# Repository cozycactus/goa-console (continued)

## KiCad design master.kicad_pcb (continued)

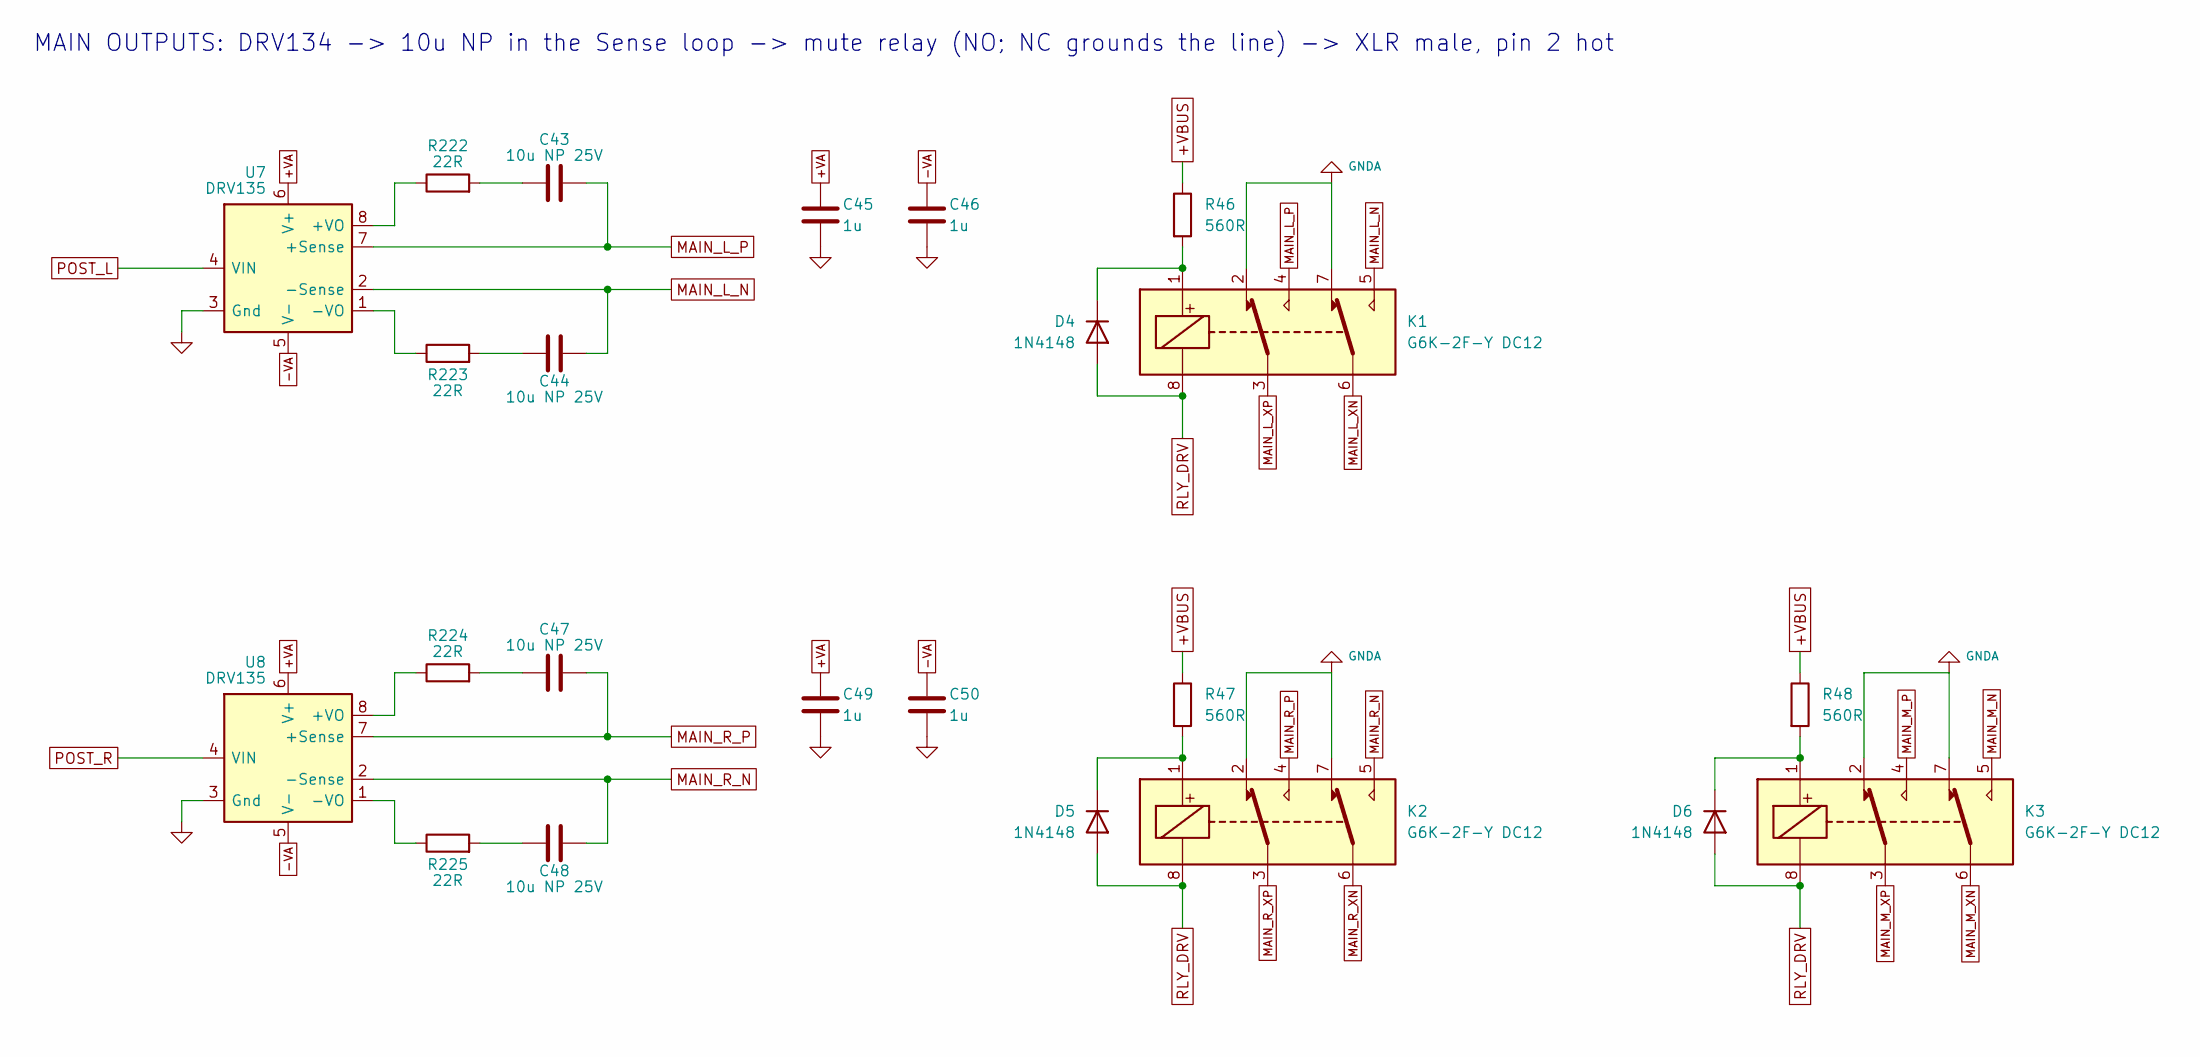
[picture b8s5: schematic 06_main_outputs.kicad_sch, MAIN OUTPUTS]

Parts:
C43, C44, C47, C48: 10u NP 25V; CP_Radial_D5.0mm_P2.00mm; MPN Panasonic ECE-A1EN100U (matched pair: t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
C45, C46, C49, C50: 1u; C_1206_3216Metric; MPN Samsung CL31B105KBHNNNE (X7R 50V)
D4, D5, D6: 1N4148; D_DO-35_SOD27_P7.62mm_Horizontal; MPN Vishay 1N4148-TAP
K1, K2, K3: G6K-2F-Y DC12; Relay_DPDT_Omron_G6K-2F-Y; MPN Omron G6K-2F-Y DC12
R46, R47, R48: 560R; R_0805_2012Metric
R222, R223, R224, R225: 22R; R_0805_2012Metric; MPN Panasonic ERJ-P06J220V
U7, U8: DRV135; SOIC-8_3.9x4.9mm_P1.27mm; MPN TI DRV135UA

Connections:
+VA: C45.1, C49.1, U7.6 (V+), U8.6 (V+); also elsewhere on the board
+VBUS: R46.1, R47.1, R48.1; also elsewhere on the board
-VA: C46.2, C50.2, U7.5 (V-), U8.5 (V-); also elsewhere on the board
MAIN_L_N: C44.2, K1.5, U7.2 (-Sense)
MAIN_L_P: C43.2, K1.4, U7.7 (+Sense)
MAIN_L_XN: K1.6; also elsewhere on the board
MAIN_L_XP: K1.3; also elsewhere on the board
MAIN_M_N: K3.5; also elsewhere on the board
MAIN_M_P: K3.4; also elsewhere on the board
MAIN_M_XN: K3.6; also elsewhere on the board
MAIN_M_XP: K3.3; also elsewhere on the board
MAIN_R_N: C48.2, K2.5, U8.2 (-Sense)
MAIN_R_P: C47.2, K2.4, U8.7 (+Sense)
MAIN_R_XN: K2.6; also elsewhere on the board
MAIN_R_XP: K2.3; also elsewhere on the board
unnamed: C43.1, R222.2
unnamed: C44.1, R223.2
unnamed: C47.1, R224.2
unnamed: C48.1, R225.2
unnamed: D4.1 (K), K1.1, R46.2
unnamed: D5.1 (K), K2.1, R47.2
unnamed: D6.1 (K), K3.1, R48.2
unnamed: R222.1, U7.8 (+VO)
unnamed: R223.1, U7.1 (-VO)
unnamed: R224.1, U8.8 (+VO)
unnamed: R225.1, U8.1 (-VO)
POST_L: U7.4 (VIN); also elsewhere on the board
POST_R: U8.4 (VIN); also elsewhere on the board
RLY_DRV: D4.2 (A), D5.2 (A), D6.2 (A), K1.8, K2.8, K3.8; also elsewhere on the board

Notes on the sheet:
MAIN OUTPUTS: DRV134 -> 10u NP in the Sense loop -> mute relay (NO; NC grounds the line) -> XLR male, pin 2 hot

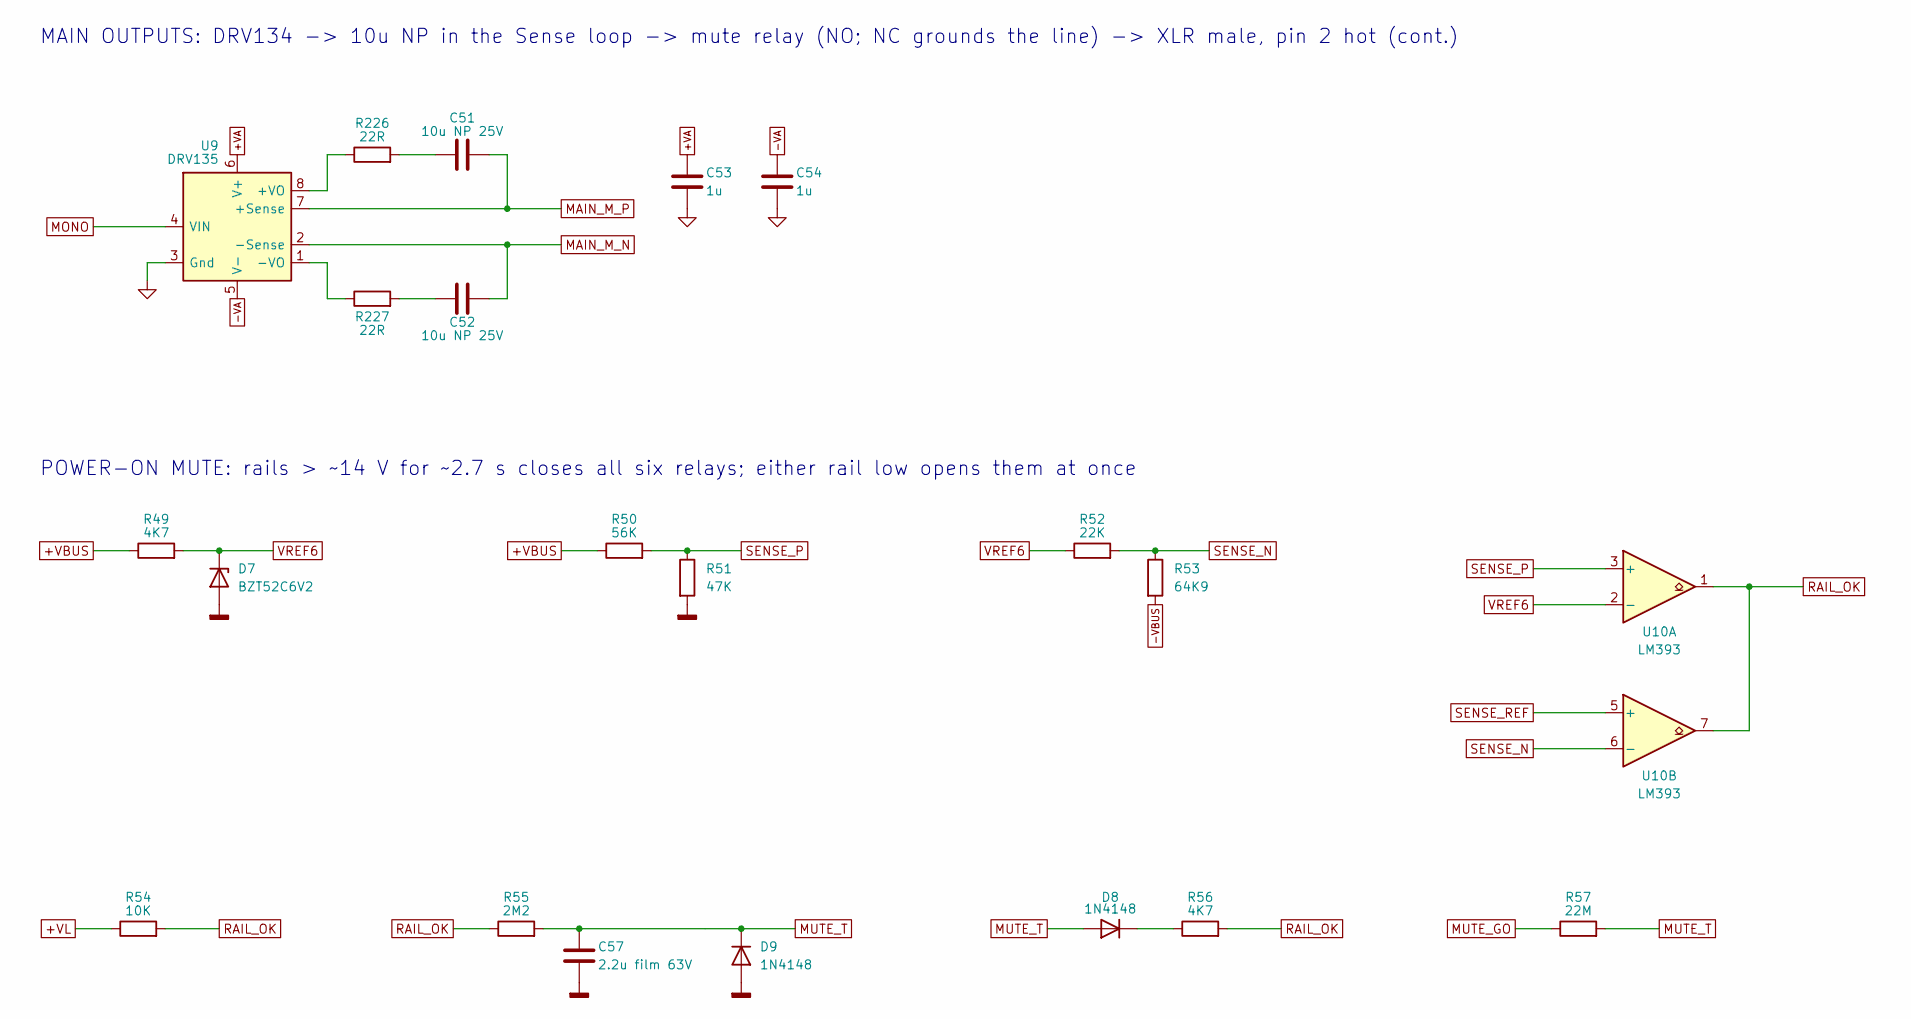
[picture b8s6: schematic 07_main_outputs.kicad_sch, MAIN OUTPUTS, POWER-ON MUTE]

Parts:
C51, C52: 10u NP 25V; CP_Radial_D5.0mm_P2.00mm; MPN Panasonic ECE-A1EN100U (matched pair: t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
C53, C54: 1u; C_1206_3216Metric; MPN Samsung CL31B105KBHNNNE (X7R 50V)
C57: 2.2u film 63V; C_Rect_L7.2mm_W7.2mm_P5.00mm_FKS2_FKP2_MKS2_MKP2; MPN KEMET MMK5225K63J06L4BULK (PET 63V; rep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
D7: BZT52C6V2; D_SOD-123; MPN Diodes BZT52C6V2-7-F
D8, D9: 1N4148; D_DO-35_SOD27_P7.62mm_Horizontal; MPN Vishay 1N4148-TAP
R49, R56: 4K7; R_0805_2012Metric
R50: 56K; R_0805_2012Metric
R51: 47K; R_0805_2012Metric
R52: 22K; R_0805_2012Metric
R53: 64K9; R_0805_2012Metric
R54: 10K; R_0805_2012Metric; MPN Panasonic ERJ-P06J103V
R55: 2M2; R_0805_2012Metric
R57: 22M; R_0805_2012Metric; MPN Yageo RC0805JR-0722ML
R226, R227: 22R; R_0805_2012Metric; MPN Panasonic ERJ-P06J220V
U9: DRV135; SOIC-8_3.9x4.9mm_P1.27mm; MPN TI DRV135UA
U10: LM393; SOIC-8_3.9x4.9mm_P1.27mm; MPN TI LM393BIDR

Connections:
+VA: C53.1, U9.6 (V+); also elsewhere on the board
+VBUS: R49.1, R50.1; also elsewhere on the board
+VL: R54.1; also elsewhere on the board
-VA: C54.2, U9.5 (V-); also elsewhere on the board
-VBUS: R53.2; also elsewhere on the board
GNDD: C57.2, D7.2 (A), D9.2 (A), R51.2; also elsewhere on the board
MAIN_M_N: C52.2, U9.2 (-Sense); also elsewhere on the board
MAIN_M_P: C51.2, U9.7 (+Sense); also elsewhere on the board
MONO: U9.4 (VIN); also elsewhere on the board
MUTE_GO: R57.1; also elsewhere on the board
MUTE_T: C57.1, D8.2 (A), D9.1 (K), R55.2, R57.2; also elsewhere on the board
unnamed: C51.1, R226.2
unnamed: C52.1, R227.2
unnamed: D8.1 (K), R56.1
unnamed: R226.1, U9.8 (+VO)
unnamed: R227.1, U9.1 (-VO)
RAIL_OK: R54.2, R55.1, R56.2, U10.1, U10.7; also elsewhere on the board
SENSE_N: R52.2, R53.1, U10.6 (-)
SENSE_P: R50.2, R51.1, U10.3 (+)
SENSE_REF: U10.5 (+); also elsewhere on the board
VREF6: D7.1 (K), R49.2, R52.1, U10.2 (-); also elsewhere on the board

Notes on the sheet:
MAIN OUTPUTS: DRV134 -> 10u NP in the Sense loop -> mute relay (NO; NC grounds the line) -> XLR male, pin 2 hot (cont.)
POWER-ON MUTE: rails > ~14 V for ~2.7 s closes all six relays; either rail low opens them at once

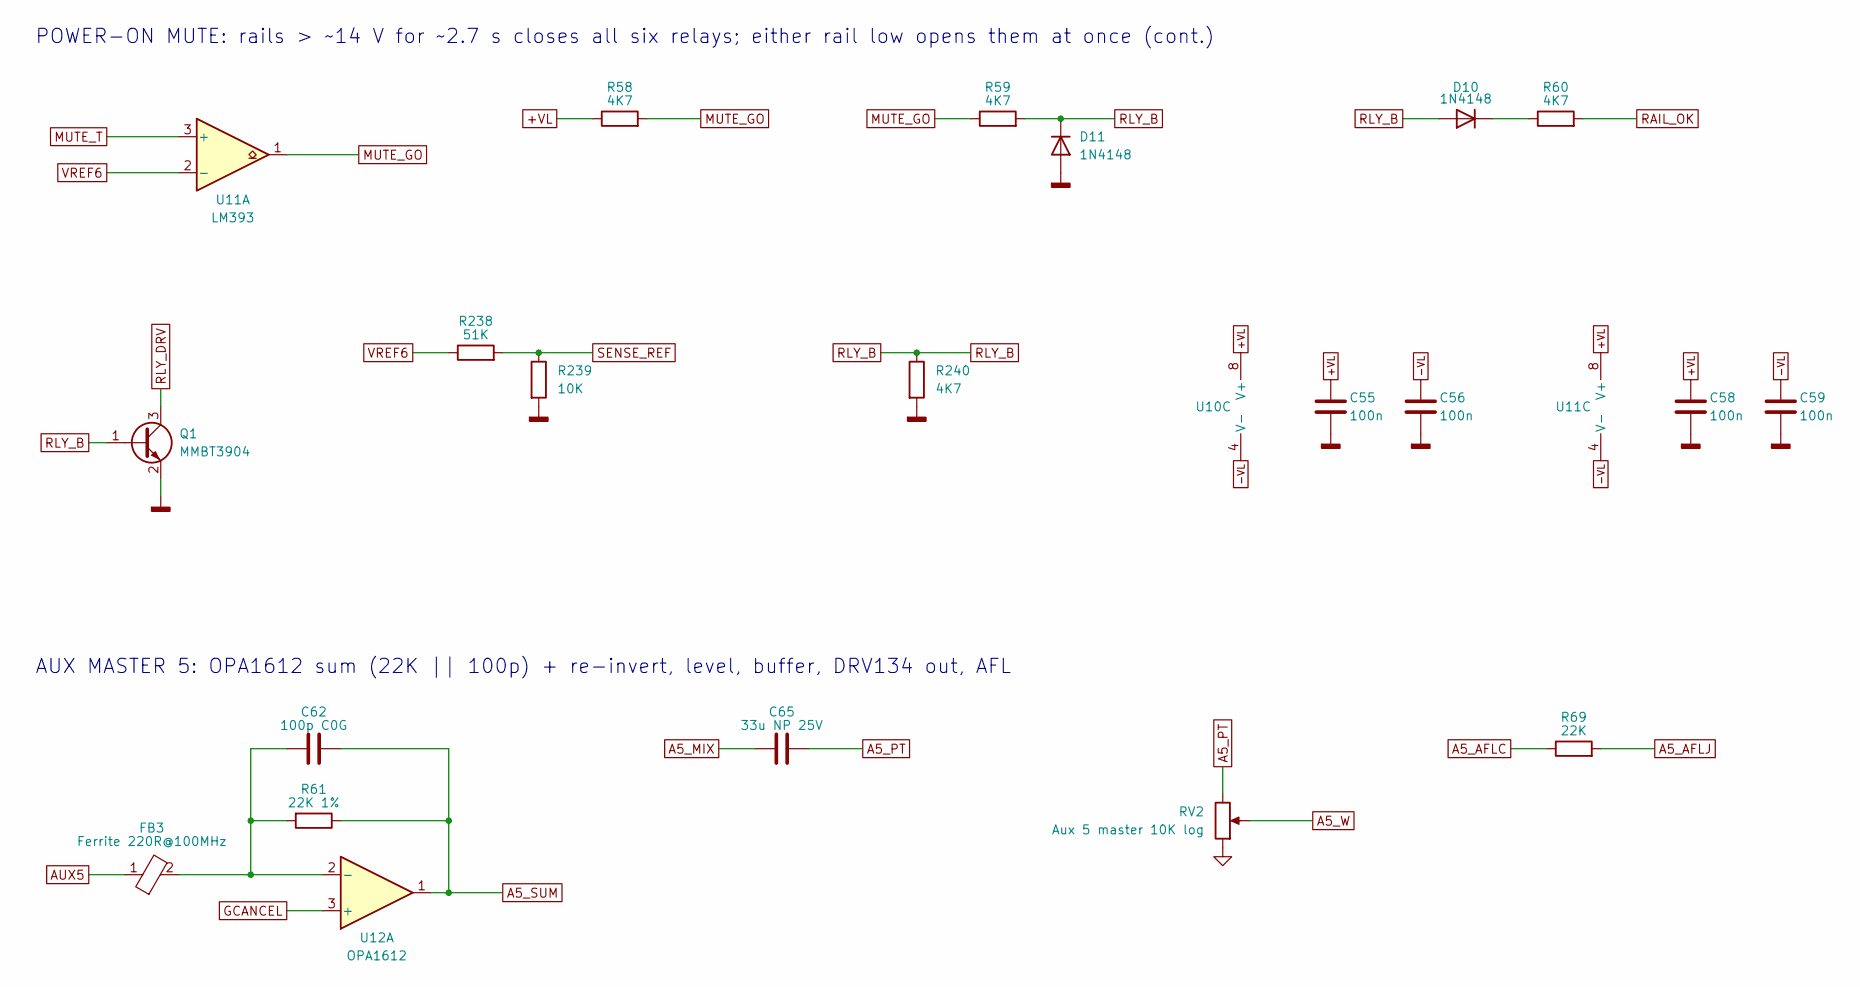
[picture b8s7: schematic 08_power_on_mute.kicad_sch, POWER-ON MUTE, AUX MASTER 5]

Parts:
C55, C56, C58, C59: 100n; C_0805_2012Metric; MPN Samsung CL21B104KBCNNNC (X7R 50V)
C62: 100p C0G; C_0805_2012Metric; MPN KEMET C0805C101J5GACTU
C65: 33u NP 25V; CP_Radial_D8.0mm_P3.50mm; MPN Nichicon UES1E330MPM (MUSE ES)
D10, D11: 1N4148; D_DO-35_SOD27_P7.62mm_Horizontal; MPN Vishay 1N4148-TAP
FB3: Ferrite 220R@100MHz; L_0805_2012Metric; MPN Murata BLM21PG221SN1D
Q1: MMBT3904; SOT-23; MPN onsemi MMBT3904LT1G
R58: 4K7; R_0805_2012Metric; MPN Panasonic ERJ-P06J472V
R59, R60, R240: 4K7; R_0805_2012Metric
R61: 22K 1%; R_0805_2012Metric
R69: 22K; R_0805_2012Metric
R238: 51K; R_0805_2012Metric
R239: 10K; R_0805_2012Metric
RV2: Aux 5 master 10K log; Potentiometer_Alpha_RD901F-40-00D_Single_Vertical; MPN Alpha RD901F-40-15R1-A10K
U10, U11: LM393; SOIC-8_3.9x4.9mm_P1.27mm; MPN TI LM393BIDR
U12: OPA1612; SOIC-8_3.9x4.9mm_P1.27mm; MPN TI OPA1612AIDR

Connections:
+VL: C55.1, C58.1, R58.1, U10.8 (V+), U11.8 (V+); also elsewhere on the board
-VL: C56.2, C59.2, U10.4 (V-), U11.4 (V-); also elsewhere on the board
A5_AFLC: R69.1; also elsewhere on the board
A5_AFLJ: R69.2; also elsewhere on the board
A5_MIX: C65.1; also elsewhere on the board
A5_PT: C65.2, RV2.3
A5_SUM: C62.1, R61.1, U12.1; also elsewhere on the board
A5_W: RV2.2; also elsewhere on the board
AUX5: FB3.1; also elsewhere on the board
GCANCEL: U12.3 (+); also elsewhere on the board
GNDD: C55.2, C56.1, C58.2, C59.1, D11.2 (A), Q1.2 (E), R239.2, R240.2; also elsewhere on the board
MUTE_GO: R58.2, R59.1, U11.1; also elsewhere on the board
MUTE_T: U11.3 (+); also elsewhere on the board
unnamed: D10.1 (K), R60.1
unnamed: C62.2, FB3.2, R61.2, U12.2 (-)
RAIL_OK: R60.2; also elsewhere on the board
RLY_B: D10.2 (A), D11.1 (K), Q1.1 (B), R59.2, R240.1
RLY_DRV: Q1.3 (C); also elsewhere on the board
SENSE_REF: R238.2, R239.1; also elsewhere on the board
VREF6: R238.1, U11.2 (-); also elsewhere on the board

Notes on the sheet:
POWER-ON MUTE: rails > ~14 V for ~2.7 s closes all six relays; either rail low opens them at once (cont.)
AUX MASTER 5: OPA1612 sum (22K || 100p) + re-invert, level, buffer, DRV134 out, AFL

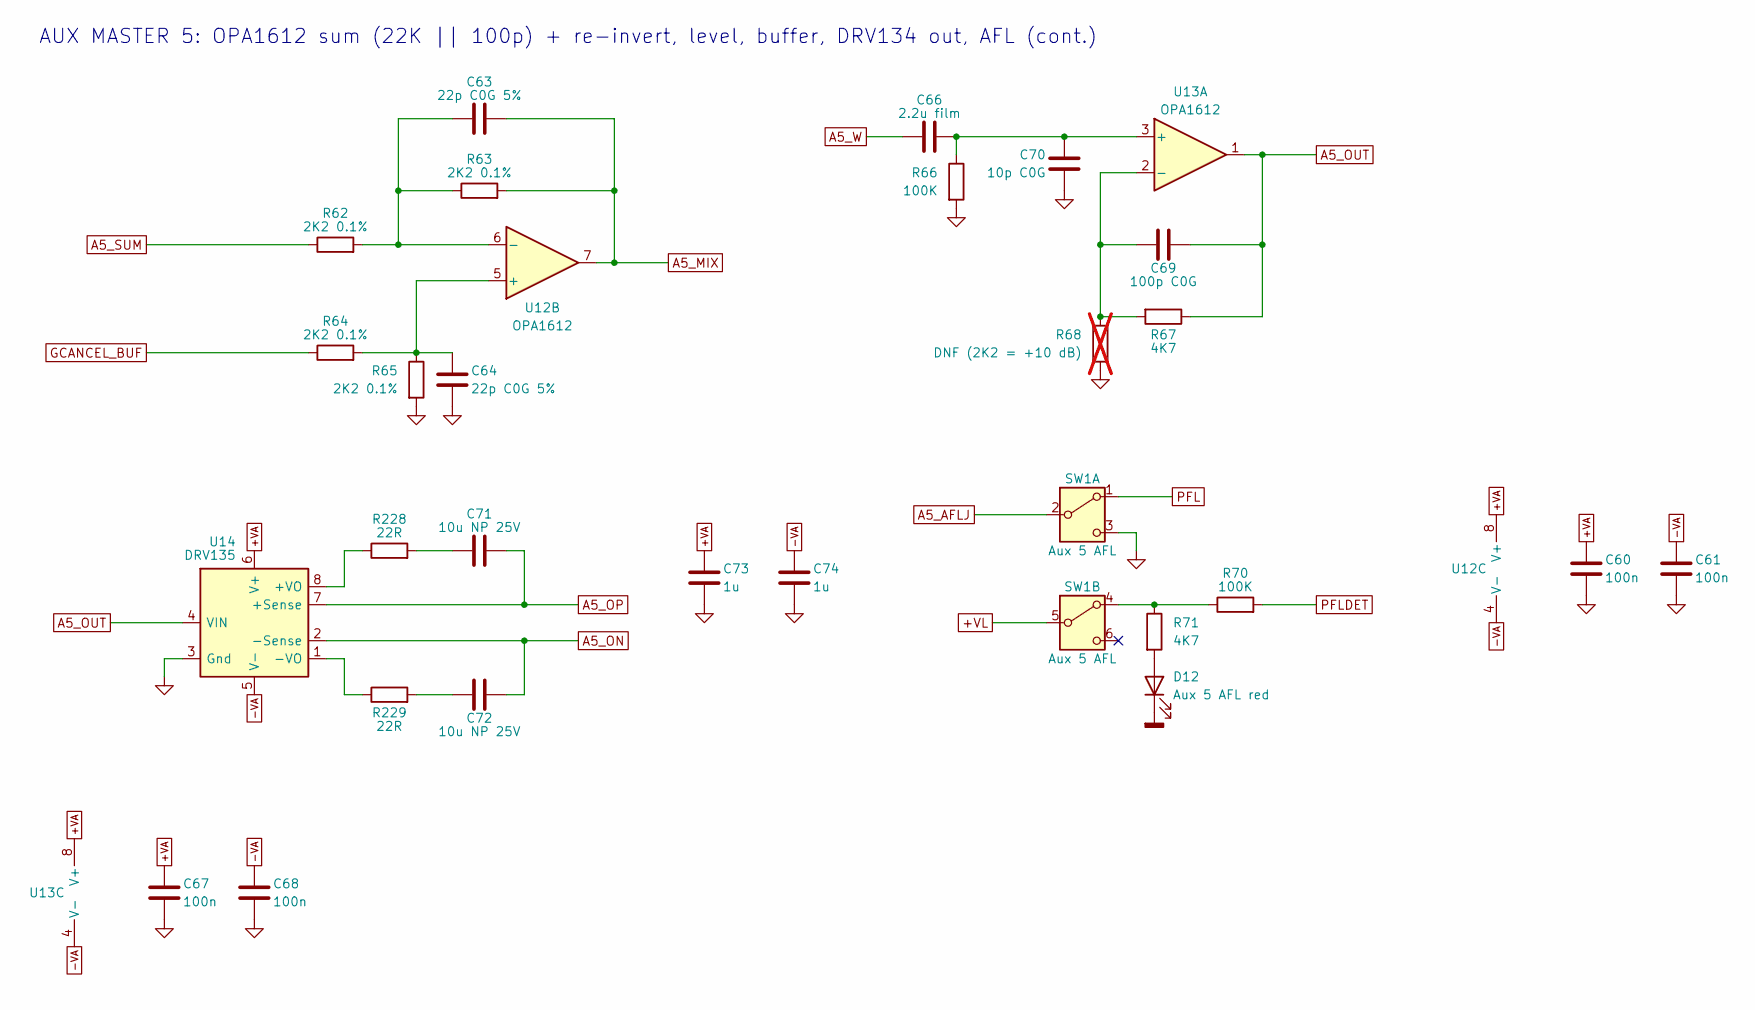
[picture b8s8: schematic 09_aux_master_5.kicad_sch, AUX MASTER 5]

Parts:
C60, C61, C67, C68: 100n; C_0805_2012Metric; MPN Samsung CL21B104KBCNNNC (X7R 50V)
C63, C64: 22p C0G 5%; C_0805_2012Metric; MPN KEMET C0805C220J5GACTU
C66: 2.2u film; C_Rect_L7.2mm_W7.2mm_P5.00mm_FKS2_FKP2_MKS2_MKP2; MPN KEMET MMK5225K63J06L4BULK (PET 63V; rep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
C69: 100p C0G; C_0805_2012Metric; MPN KEMET C0805C101J5GACTU
C70: 10p C0G; C_0805_2012Metric; MPN KEMET C0805C100J5GACTU
C71, C72: 10u NP 25V; CP_Radial_D5.0mm_P2.00mm; MPN Panasonic ECE-A1EN100U (matched pair: t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
C73, C74: 1u; C_1206_3216Metric; MPN Samsung CL31B105KBHNNNE (X7R 50V)
D12: Aux 5 AFL red; LED_D3.0mm; MPN Kingbright WP710A10ID
R62, R63, R64, R65: 2K2 0.1%; R_0805_2012Metric; MPN Panasonic ERA-6AEB222V
R66, R70: 100K; R_0805_2012Metric
R67, R71: 4K7; R_0805_2012Metric
R68: DNF (2K2 = +10 dB); R_0805_2012Metric; not fitted
R228, R229: 22R; R_0805_2012Metric; MPN Panasonic ERJ-P06J220V
SW1: Aux 5 AFL; SW_Push_2P2T_Toggle_CK_PVA2xxH1xxxxxxV2; MPN C&K PVA2 EE H1 1.7N V2
U12, U13: OPA1612; SOIC-8_3.9x4.9mm_P1.27mm; MPN TI OPA1612AIDR
U14: DRV135; SOIC-8_3.9x4.9mm_P1.27mm; MPN TI DRV135UA

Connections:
+VA: C60.1, C67.1, C73.1, U12.8 (V+), U13.8 (V+), U14.6 (V+); also elsewhere on the board
+VL: SW1.5 (B); also elsewhere on the board
-VA: C61.2, C68.2, C74.2, U12.4 (V-), U13.4 (V-), U14.5 (V-); also elsewhere on the board
A5_AFLJ: SW1.2 (B); also elsewhere on the board
A5_MIX: C63.1, R63.2, U12.7; also elsewhere on the board
A5_ON: C72.2, U14.2 (-Sense); also elsewhere on the board
A5_OP: C71.2, U14.7 (+Sense); also elsewhere on the board
A5_OUT: C69.1, R67.1, U13.1, U14.4 (VIN); also elsewhere on the board
A5_SUM: R62.1; also elsewhere on the board
A5_W: C66.1; also elsewhere on the board
GCANCEL_BUF: R64.1; also elsewhere on the board
GNDD: D12.1 (K); also elsewhere on the board
unnamed: C71.1, R228.2
unnamed: C72.1, R229.2
unnamed: D12.2 (A), R71.2
unnamed: R70.1, R71.1, SW1.4 (A)
unnamed: C64.1, R64.2, R65.1, U12.5 (+)
unnamed: C63.2, R62.2, R63.1, U12.6 (-)
unnamed: C66.2, C70.1, R66.1, U13.3 (+)
unnamed: C69.2, R67.2, R68.1, U13.2 (-)
unnamed: R228.1, U14.8 (+VO)
unnamed: R229.1, U14.1 (-VO)
PFL: SW1.1 (A); also elsewhere on the board
PFLDET: R70.2; also elsewhere on the board

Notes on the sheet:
AUX MASTER 5: OPA1612 sum (22K || 100p) + re-invert, level, buffer, DRV134 out, AFL (cont.)

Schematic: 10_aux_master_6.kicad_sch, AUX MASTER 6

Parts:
C75, C76: 100n; C_0805_2012Metric; MPN Samsung CL21B104KBCNNNC (X7R 50V)
C77, C82: 100p C0G; C_0805_2012Metric; MPN KEMET C0805C101J5GACTU
C78, C79: 22p C0G 5%; C_0805_2012Metric; MPN KEMET C0805C220J5GACTU
C80: 33u NP 25V; CP_Radial_D8.0mm_P3.50mm; MPN Nichicon UES1E330MPM (MUSE ES)
C81: 2.2u film; C_Rect_L7.2mm_W7.2mm_P5.00mm_FKS2_FKP2_MKS2_MKP2; MPN KEMET MMK5225K63J06L4BULK (PET 63V; rep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
C83: 10p C0G; C_0805_2012Metric; MPN KEMET C0805C100J5GACTU
C84, C85: 10u NP 25V; CP_Radial_D5.0mm_P2.00mm; MPN Panasonic ECE-A1EN100U (matched pair: t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
C86, C87: 1u; C_1206_3216Metric; MPN Samsung CL31B105KBHNNNE (X7R 50V)
FB4: Ferrite 220R@100MHz; L_0805_2012Metric; MPN Murata BLM21PG221SN1D
R72: 22K 1%; R_0805_2012Metric
R73, R74, R75, R76: 2K2 0.1%; R_0805_2012Metric; MPN Panasonic ERA-6AEB222V
R77: 100K; R_0805_2012Metric
R78: 4K7; R_0805_2012Metric
R79: DNF (2K2 = +10 dB); R_0805_2012Metric; not fitted
R80: 22K; R_0805_2012Metric
R230, R231: 22R; R_0805_2012Metric; MPN Panasonic ERJ-P06J220V
RV3: Aux 6 master 10K log; Potentiometer_Alpha_RD901F-40-00D_Single_Vertical; MPN Alpha RD901F-40-15R1-A10K
U13, U15: OPA1612; SOIC-8_3.9x4.9mm_P1.27mm; MPN TI OPA1612AIDR
U16: DRV135; SOIC-8_3.9x4.9mm_P1.27mm; MPN TI DRV135UA

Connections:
+VA: C75.1, C86.1, U15.8 (V+), U16.6 (V+); also elsewhere on the board
-VA: C76.2, C87.2, U15.4 (V-), U16.5 (V-); also elsewhere on the board
A6_AFLJ: R80.2; also elsewhere on the board
A6_MIX: C78.1, C80.1, R74.2, U15.7
A6_ON: C85.2, U16.2 (-Sense); also elsewhere on the board
A6_OP: C84.2, U16.7 (+Sense); also elsewhere on the board
A6_PT: C80.2, RV3.3
A6_SUM: C77.1, R72.1, R73.1, U15.1
A6_W: C81.1, RV3.2
AUX6: FB4.1; also elsewhere on the board
GCANCEL: U15.3 (+); also elsewhere on the board
GCANCEL_BUF: R75.1; also elsewhere on the board
unnamed: C84.1, R230.2
unnamed: C85.1, R231.2
unnamed: C81.2, C83.1, R77.1, U13.5 (+)
unnamed: C82.2, R78.2, R79.1, U13.6 (-)
unnamed: C77.2, FB4.2, R72.2, U15.2 (-)
unnamed: C79.1, R75.2, R76.1, U15.5 (+)
unnamed: C78.2, R73.2, R74.1, U15.6 (-)
unnamed: R230.1, U16.8 (+VO)
unnamed: R231.1, U16.1 (-VO)

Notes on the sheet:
AUX MASTER 6: OPA1612 sum (22K || 100p) + re-invert, level, buffer, DRV134 out, AFL

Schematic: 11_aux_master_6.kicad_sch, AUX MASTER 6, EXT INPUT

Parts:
C88, C89: 100p C0G; C_0805_2012Metric; MPN KEMET C0805C101J5GACTU
C90, C91: 33p C0G; C_0805_2012Metric; MPN KEMET C0805C330J5GACTU
C98, C99: 33u NP 25V; CP_Radial_D8.0mm_P3.50mm; MPN Nichicon UES1E330MPM (MUSE ES)
D13: Aux 6 AFL red; LED_D3.0mm; MPN Kingbright WP710A10ID
R81: 100K; R_0805_2012Metric
R82: 4K7; R_0805_2012Metric
R83, R212: 1M; R_0805_2012Metric
R84, R85, R86, R87: 10K 0.1%; R_0805_2012Metric; MPN Panasonic ERA-6AEB103V
R93, R95, R215, R216: 100R; R_0805_2012Metric
R94, R96: 47K; R_0805_2012Metric
R213, R214: 220R; R_0805_2012Metric
SW2: Aux 6 AFL; SW_Push_2P2T_Toggle_CK_PVA2xxH1xxxxxxV2; MPN C&K PVA2 EE H1 1.7N V2
U17: OPA1612; SOIC-8_3.9x4.9mm_P1.27mm; MPN TI OPA1612AIDR
U43: OPA1656; SOIC-8_3.9x4.9mm_P1.27mm; MPN TI OPA1656IDR

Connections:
+VL: SW2.5 (B); also elsewhere on the board
A6_AFLJ: SW2.2 (B); also elsewhere on the board
EXT_BL: C90.2, R85.2, R93.1, U17.1
EXT_BL_RB: R84.1, R216.2
EXT_BL_TB: R86.1, R215.2
EXT_BR: R95.1; also elsewhere on the board
EXT_L: C98.2, R94.1; also elsewhere on the board
EXT_LR: R212.1, R214.1; also elsewhere on the board
EXT_LT: R83.1, R213.1; also elsewhere on the board
EXT_R: C99.2, R96.1; also elsewhere on the board
GNDD: D13.1 (K); also elsewhere on the board
unnamed: C98.1, R93.2
unnamed: C99.1, R95.2
unnamed: D13.2 (A), R82.2
unnamed: R81.1, R82.1, SW2.4 (A)
unnamed: C91.1, R86.2, R87.1, U17.3 (+)
unnamed: C90.1, R84.2, R85.1, U17.2 (-)
unnamed: C88.1, R213.2, U43.3 (+)
unnamed: R215.1, U43.1, U43.2 (-)
unnamed: C89.1, R214.2, U43.5 (+)
unnamed: R216.1, U43.6 (-), U43.7
PFL: SW2.1 (A); also elsewhere on the board
PFLDET: R81.2; also elsewhere on the board

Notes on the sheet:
AUX MASTER 6: OPA1612 sum (22K || 100p) + re-invert, level, buffer, DRV134 out, AFL (cont.)
EXT INPUT (2-track / DAW) and MIX / EXT monitor select (SW latched = EXT)

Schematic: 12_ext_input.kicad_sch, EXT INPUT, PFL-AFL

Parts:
C92, C93, C100, C101, C190, C191, C192, C193: 100n; C_0805_2012Metric; MPN Samsung CL21B104KBCNNNC (X7R 50V)
C94, C95: 100p C0G; C_0805_2012Metric; MPN KEMET C0805C101J5GACTU
C96, C97: 33p C0G; C_0805_2012Metric; MPN KEMET C0805C330J5GACTU
C105: 33u NP 25V; CP_Radial_D8.0mm_P3.50mm; MPN Nichicon UES1E330MPM (MUSE ES)
C106: 2.2u film; C_Rect_L7.2mm_W7.2mm_P5.00mm_FKS2_FKP2_MKS2_MKP2; MPN KEMET MMK5225K63J06L4BULK (PET 63V; rep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
C109: 22p C0G; C_0805_2012Metric; MPN KEMET C0805C220J5GACTU
R88, R217: 1M; R_0805_2012Metric
R89, R90, R91, R92: 10K 0.1%; R_0805_2012Metric; MPN Panasonic ERA-6AEB103V
R102: 100K; R_0805_2012Metric
R103, R220, R221: 100R; R_0805_2012Metric
R218, R219: 220R; R_0805_2012Metric
RV4: Solo level 10K log; Potentiometer_Alpha_RD901F-40-00D_Single_Vertical; MPN Alpha RD901F-40-15R1-A10K
SW3: EXT select; SW_Push_2P2T_Toggle_CK_PVA2xxH1xxxxxxV2; MPN C&K PVA2 EE H1 1.7N V2
U17, U19: OPA1612; SOIC-8_3.9x4.9mm_P1.27mm; MPN TI OPA1612AIDR
U18, U43, U44: OPA1656; SOIC-8_3.9x4.9mm_P1.27mm; MPN TI OPA1656IDR

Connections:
+VA: C92.1, C100.1, C190.1, C192.1, U17.8 (V+), U18.8 (V+), U43.8 (V+), U44.8 (V+); also elsewhere on the board
-VA: C93.2, C101.2, C191.2, C193.2, U17.4 (V-), U18.4 (V-), U43.4 (V-), U44.4 (V-); also elsewhere on the board
EXT_BR: C96.2, R90.2, U17.7; also elsewhere on the board
EXT_BR_RB: R89.1, R221.2
EXT_BR_TB: R91.1, R220.2
EXT_L: SW3.1 (A); also elsewhere on the board
EXT_R: SW3.4 (A); also elsewhere on the board
EXT_RR: R217.1, R219.1; also elsewhere on the board
EXT_RT: R88.1, R218.1; also elsewhere on the board
MON_L: SW3.2 (B); also elsewhere on the board
MON_R: SW3.5 (B); also elsewhere on the board
unnamed: C97.1, R91.2, R92.1, U17.5 (+)
unnamed: C96.1, R89.2, R90.1, U17.6 (-)
unnamed: C106.2, C109.1, R102.1, U19.3 (+)
unnamed: R103.1, U19.1, U19.2 (-)
unnamed: C94.1, R218.2, U44.3 (+)
unnamed: R220.1, U44.1, U44.2 (-)
unnamed: C95.1, R219.2, U44.5 (+)
unnamed: R221.1, U44.6 (-), U44.7
PFL_MIX: C105.1; also elsewhere on the board
PFL_PT: C105.2, RV4.3
PFL_SIG: R103.2; also elsewhere on the board
PFL_W: C106.1, RV4.2
POST_L: SW3.3 (C); also elsewhere on the board
POST_R: SW3.6 (C); also elsewhere on the board

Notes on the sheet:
EXT INPUT (2-track / DAW) and MIX / EXT monitor select (cont.)
PFL / AFL: OPA1656 sum (22K || 100p) + re-invert, SOLO LEVEL, follower

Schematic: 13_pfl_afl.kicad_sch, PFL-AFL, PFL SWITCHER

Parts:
C102: 100p C0G; C_0805_2012Metric; MPN KEMET C0805C101J5GACTU
C103, C104: 22p C0G 5%; C_0805_2012Metric; MPN KEMET C0805C220J5GACTU
C107, C108: 100n; C_0805_2012Metric; MPN Samsung CL21B104KBCNNNC (X7R 50V)
C110: 1u; C_1206_3216Metric; MPN Samsung CL31B105KBHNNNE (X7R 50V)
C111, C112, C113, C114: 33u NP 25V; CP_Radial_D8.0mm_P3.50mm; MPN Nichicon UES1E330MPM (MUSE ES)
D14: BZX84C5V1; SOT-23; MPN Diodes BZX84C5V1-7-F
D15: BAT54W; SOT-323_SC-70; MPN Nexperia BAT54W,115
FB5: Ferrite 220R@100MHz; L_0805_2012Metric; MPN Murata BLM21PG221SN1D
R97: 22K 1%; R_0805_2012Metric
R98, R99, R100, R101: 2K2 0.1%; R_0805_2012Metric; MPN Panasonic ERA-6AEB222V
R104: 4K7; R_0805_2012Metric
R105, R106, R107, R108: 1M; R_0805_2012Metric
R109: 100K; R_0805_2012Metric
U18, U21: OPA1656; SOIC-8_3.9x4.9mm_P1.27mm; MPN TI OPA1656IDR
U19: OPA1612; SOIC-8_3.9x4.9mm_P1.27mm; MPN TI OPA1612AIDR

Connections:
+5VL: C110.1, D14.3 (K), D15.1 (A), R104.2; also elsewhere on the board
+VA: C107.1, D15.3 (K), R104.1, U19.8 (V+); also elsewhere on the board
-VA: C108.2, U19.4 (V-); also elsewhere on the board
CRSB_LO: U21.1, U21.2 (-); also elsewhere on the board
CRS_L: R109.1, U21.3 (+); also elsewhere on the board
GCANCEL: U18.3 (+); also elsewhere on the board
GCANCEL_BUF: R100.1; also elsewhere on the board
GNDD: C110.2, D14.1 (A); also elsewhere on the board
MON_L: C111.1; also elsewhere on the board
MON_R: C113.1; also elsewhere on the board
unnamed: C102.2, FB5.2, R97.2, U18.2 (-)
unnamed: C104.1, R100.2, R101.1, U18.5 (+)
unnamed: C103.2, R98.2, R99.1, U18.6 (-)
PFL: FB5.1; also elsewhere on the board
PFL_MIX: C103.1, R99.2, U18.7; also elsewhere on the board
PFL_SIG: C112.1, C114.1; also elsewhere on the board
PFL_SUM: C102.1, R97.1, R98.1, U18.1
SWML_S: C111.2, R105.1; also elsewhere on the board
SWMR_S: C113.2, R107.1; also elsewhere on the board
SWPL_S: C112.2, R106.1; also elsewhere on the board
SWPR_S: C114.2, R108.1; also elsewhere on the board

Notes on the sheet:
PFL / AFL: OPA1656 sum (22K || 100p) + re-invert, SOLO LEVEL, follower (cont.)
PFL SWITCHER: DG413 (PFL pressed = SW1/SW4, else SW2/SW3; break-before-make) -> CRS L/R OPA1656 followers

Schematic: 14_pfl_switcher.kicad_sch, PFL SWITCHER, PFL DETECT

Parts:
C115, C116, C117, C118, C119: 100n; C_0805_2012Metric; MPN Samsung CL21B104KBCNNNC (X7R 50V)
C120: 1u; C_1206_3216Metric; MPN Samsung CL31B105KBHNNNE (X7R 50V)
D16, D17: 1N4148; D_DO-35_SOD27_P7.62mm_Horizontal; MPN Vishay 1N4148-TAP
R110, R112: 100R; R_0805_2012Metric
R111, R116: 100K; R_0805_2012Metric
R113, R115: 10K; R_0805_2012Metric
R114: 330K; R_0805_2012Metric
R117: 10M; R_0805_2012Metric
U20: DG413; SOIC-16_3.9x9.9mm_P1.27mm; MPN Vishay DG413DY-E3
U21: OPA1656; SOIC-8_3.9x4.9mm_P1.27mm; MPN TI OPA1656IDR

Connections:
+5VL: C115.1, R116.1, U20.12 (VL); also elsewhere on the board
+VA: C116.1, C118.1, U20.13 (V+), U21.8 (V+); also elsewhere on the board
+VL: R114.1; also elsewhere on the board
-VA: C117.2, C119.2, U20.4 (V-), U21.4 (V-); also elsewhere on the board
CRSB_L: R110.2; also elsewhere on the board
CRSB_LO: R110.1; also elsewhere on the board
CRSB_R: R112.2; also elsewhere on the board
CRSB_RO: R112.1, U21.6 (-), U21.7
CRS_L: U20.2, U20.15; also elsewhere on the board
CRS_R: R111.1, U20.7, U20.10, U21.5 (+)
GNDD: C115.2, C120.2, D17.1 (K), R113.2, R115.2, U20.5 (GND); also elsewhere on the board
unnamed: D16.1 (K), D17.2 (A)
PFLDET: C120.1, D16.2 (A), R113.1, R117.2; also elsewhere on the board
PFL_ON: U20.1, U20.8, U20.9, U20.16; also elsewhere on the board
PFL_ON_RAW: R116.2, R117.1; also elsewhere on the board
PFL_REF: R114.2, R115.1; also elsewhere on the board
SWML_S: U20.14; also elsewhere on the board
SWMR_S: U20.11; also elsewhere on the board
SWPL_S: U20.3; also elsewhere on the board
SWPR_S: U20.6; also elsewhere on the board

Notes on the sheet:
PFL SWITCHER: DG413 (PFL pressed = SW1/SW4, else SW2/SW3; break-before-make) -> CRS L/R OPA1656 followers (cont.)
PFL DETECT (0.92 V per press vs 0.50 V; 2 x 1N4148 clamp, 1u debounce) and DG413 logic, beside the switcher

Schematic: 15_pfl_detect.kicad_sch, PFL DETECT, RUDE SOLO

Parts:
C121, C122: 100n; C_0805_2012Metric; MPN Samsung CL21B104KBCNNNC (X7R 50V)
C123: 330n; C_0805_2012Metric; MPN Samsung CL21B334KBFNNNE (X7R 50V)
D18: 1N4148; D_DO-35_SOD27_P7.62mm_Horizontal; MPN Vishay 1N4148-TAP
D19: PFL ACTIVE red 5mm; LED_D5.0mm; MPN Kingbright WP7113ID
R118, R123: 10K; R_0805_2012Metric
R119, R120, R121: 100K; R_0805_2012Metric
R122: 1M; R_0805_2012Metric
R124: 3K3; R_0805_2012Metric; MPN Panasonic ERJ-P06J332V
U11, U22: LM393; SOIC-8_3.9x4.9mm_P1.27mm; MPN TI LM393BIDR

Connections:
+VL: C121.1, R119.1, R123.1, R124.1, U22.8 (V+); also elsewhere on the board
-VL: C122.2, U22.4 (V-); also elsewhere on the board
FL_HOLD: D18.1 (K), U22.7
FL_N: C123.1, D18.2 (A), R122.2, U11.6 (-)
FL_OUT: D19.1 (K), R121.1, R122.1, R123.2, U11.7
FL_P: R119.2, R120.1, R121.2, U11.5 (+)
GNDD: C121.2, C122.1, C123.2, R120.2; also elsewhere on the board
unnamed: D19.2 (A), R124.2
PFLDET: U22.3 (+), U22.5 (+); also elsewhere on the board
PFL_ON: R118.2; also elsewhere on the board
PFL_ON_RAW: R118.1, U22.1; also elsewhere on the board
PFL_REF: U22.2 (-), U22.6 (-); also elsewhere on the board

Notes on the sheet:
PFL DETECT (0.92 V per press vs 0.50 V; 2 x 1N4148 clamp, 1u debounce) and DG413 logic, beside the switcher (cont.)
RUDE SOLO: ~2 Hz flasher, PFL ACTIVE LED; held off through FL_N while no key is pressed

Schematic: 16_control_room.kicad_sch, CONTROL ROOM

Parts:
C124, C128: 2.2u film; C_Rect_L7.2mm_W7.2mm_P5.00mm_FKS2_FKP2_MKS2_MKP2; MPN KEMET MMK5225K63J06L4BULK (PET 63V; rep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
C127, C129: 22p C0G; C_0805_2012Metric; MPN KEMET C0805C220J5GACTU
C130, C131: 10u NP 25V; CP_Radial_D5.0mm_P2.00mm; MPN Panasonic ECE-A1EN100U (matched pair: t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
C132, C133: 1u; C_1206_3216Metric; MPN Samsung CL31B105KBHNNNE (X7R 50V)
D20, D21: 1N4148; D_DO-35_SOD27_P7.62mm_Horizontal; MPN Vishay 1N4148-TAP
K4, K5: G6K-2F-Y DC12; Relay_DPDT_Omron_G6K-2F-Y; MPN Omron G6K-2F-Y DC12
R125, R126: 100K; R_0805_2012Metric
R127, R128: 560R; R_0805_2012Metric
R232, R233: 22R; R_0805_2012Metric; MPN Panasonic ERJ-P06J220V
R236, R237: 91K; R_0805_2012Metric
RV5: C/Room level 10K log dual; Potentiometer_Alpha_RD902F-40-00D_Dual_Vertical; MPN Alpha RD902F-40-15R1-A10K (dual, log)
SW4: C/Room DIM; SW_Push_2P2T_Toggle_CK_PVA2xxH1xxxxxxV2; MPN C&K PVA2 EE H1 1.7N V2
U23: OPA1612; SOIC-8_3.9x4.9mm_P1.27mm; MPN TI OPA1612AIDR
U24: DRV135; SOIC-8_3.9x4.9mm_P1.27mm; MPN TI DRV135UA

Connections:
+VA: C132.1, U24.6 (V+); also elsewhere on the board
+VBUS: R127.1, R128.1; also elsewhere on the board
-VA: C133.2, U24.5 (V-); also elsewhere on the board
CRL_N: C131.2, K4.5, U24.2 (-Sense)
CRL_P: C130.2, K4.4, U24.7 (+Sense)
CRL_XN: K4.6; also elsewhere on the board
CRL_XP: K4.3; also elsewhere on the board
CRO_L: U23.1, U23.2 (-), U24.4 (VIN)
CRO_R: U23.6 (-), U23.7; also elsewhere on the board
CRP_L: R236.2, RV5.3, SW4.3 (C)
CRP_R: R237.2, RV5.6, SW4.6 (C)
CRR_N: K5.5; also elsewhere on the board
CRR_P: K5.4; also elsewhere on the board
CRR_XN: K5.6; also elsewhere on the board
CRR_XP: K5.3; also elsewhere on the board
CRSB_L: R236.1, SW4.2 (B); also elsewhere on the board
CRSB_R: R237.1, SW4.5 (B); also elsewhere on the board
CRW_L: C124.1, RV5.2
CRW_R: C128.1, RV5.5
unnamed: C130.1, R232.2
unnamed: C131.1, R233.2
unnamed: D20.1 (K), K4.1, R127.2
unnamed: D21.1 (K), K5.1, R128.2
unnamed: C124.2, C127.1, R125.1, U23.3 (+)
unnamed: C128.2, C129.1, R126.1, U23.5 (+)
unnamed: R232.1, U24.8 (+VO)
unnamed: R233.1, U24.1 (-VO)
RLY_DRV: D20.2 (A), D21.2 (A), K4.8, K5.8; also elsewhere on the board

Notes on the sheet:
CONTROL ROOM: C/ROOM dual A10K, followers, DRV134, mute relays, TRS outs

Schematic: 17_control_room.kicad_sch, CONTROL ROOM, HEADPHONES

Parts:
C125, C126, C139, C140, C142, C143: 100n; C_0805_2012Metric; MPN Samsung CL21B104KBCNNNC (X7R 50V)
C134, C135: 10u NP 25V; CP_Radial_D5.0mm_P2.00mm; MPN Panasonic ECE-A1EN100U (matched pair: t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
C136, C137: 1u; C_1206_3216Metric; MPN Samsung CL31B105KBHNNNE (X7R 50V)
C138: 2.2u film; C_Rect_L7.2mm_W7.2mm_P5.00mm_FKS2_FKP2_MKS2_MKP2; MPN KEMET MMK5225K63J06L4BULK (PET 63V; rep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
C141: 22p C0G; C_0805_2012Metric; MPN KEMET C0805C220J5GACTU
C144, C145: 10u NP 25V; CP_Radial_D5.0mm_P2.00mm; MPN Panasonic ECE-A1EN100U
C146: 100p C0G; C_0805_2012Metric; MPN KEMET C0805C101J5GACTU
R129: 100K; R_0805_2012Metric
R130: 2R2; R_2512_6332Metric; MPN Vishay CRCW25122R20FKEGHP
R131: 4K7; R_0805_2012Metric
R132: 2K2; R_0805_2012Metric
R234, R235: 22R; R_0805_2012Metric; MPN Panasonic ERJ-P06J220V
RV6: Phones level 10K log dual; Potentiometer_Alpha_RD902F-40-00D_Dual_Vertical; MPN Alpha RD902F-40-15R1-A10K (dual, log)
U23, U26: OPA1612; SOIC-8_3.9x4.9mm_P1.27mm; MPN TI OPA1612AIDR
U25: DRV135; SOIC-8_3.9x4.9mm_P1.27mm; MPN TI DRV135UA
U27: LME49600; TO-263-5_TabPin3; MPN TI LME49600TS/NOPB

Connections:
+VA: C125.1, C136.1, U23.8 (V+), U25.6 (V+); also elsewhere on the board
+VP: C139.1, C142.1, C144.1, U26.8 (V+), U27.5 (V+); also elsewhere on the board
-VA: C126.2, C137.2, U23.4 (V-), U25.5 (V-); also elsewhere on the board
-VP: C140.2, C143.2, C145.2, U26.4 (V-), U27.3 (V-); also elsewhere on the board
CRO_R: U25.4 (VIN); also elsewhere on the board
CRR_N: C135.2, U25.2 (-Sense); also elsewhere on the board
CRR_P: C134.2, U25.7 (+Sense); also elsewhere on the board
CRSB_L: RV6.3; also elsewhere on the board
CRSB_R: RV6.6; also elsewhere on the board
unnamed: C134.1, R234.2
unnamed: C135.1, R235.2
unnamed: R130.1, U27.4
unnamed: R234.1, U25.8 (+VO)
unnamed: R235.1, U25.1 (-VO)
unnamed: C138.2, C141.1, R129.1, U26.3 (+)
unnamed: C146.2, R131.2, R132.1, U26.2 (-)
unnamed: C146.1, U26.1, U27.2 (IN)
PHO_L: R130.2, R131.1; also elsewhere on the board
PHW_L: C138.1, RV6.2
PHW_R: RV6.5; also elsewhere on the board
PH_GL: R132.2; also elsewhere on the board

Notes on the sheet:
CONTROL ROOM: C/ROOM dual A10K, followers, DRV134, mute relays, TRS outs (cont.)
HEADPHONES: PHONES dual A10K, OPA1612 + LME49600 composite (+9.9 dB), 2R2 out, mute relay, PHONESGND
